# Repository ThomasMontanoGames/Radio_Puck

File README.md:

# Radio_Puck
Small STM32 based ethernet connected radio puck capable of full duplex transmit and receive as well as dual RX or dual TX. Capable of rates up to 1 Mbps and completely configurable for many kinds of different modes. This radio puck has been primarily designed to be your rubber duck that transmits a known signal while prototyping a receiver.

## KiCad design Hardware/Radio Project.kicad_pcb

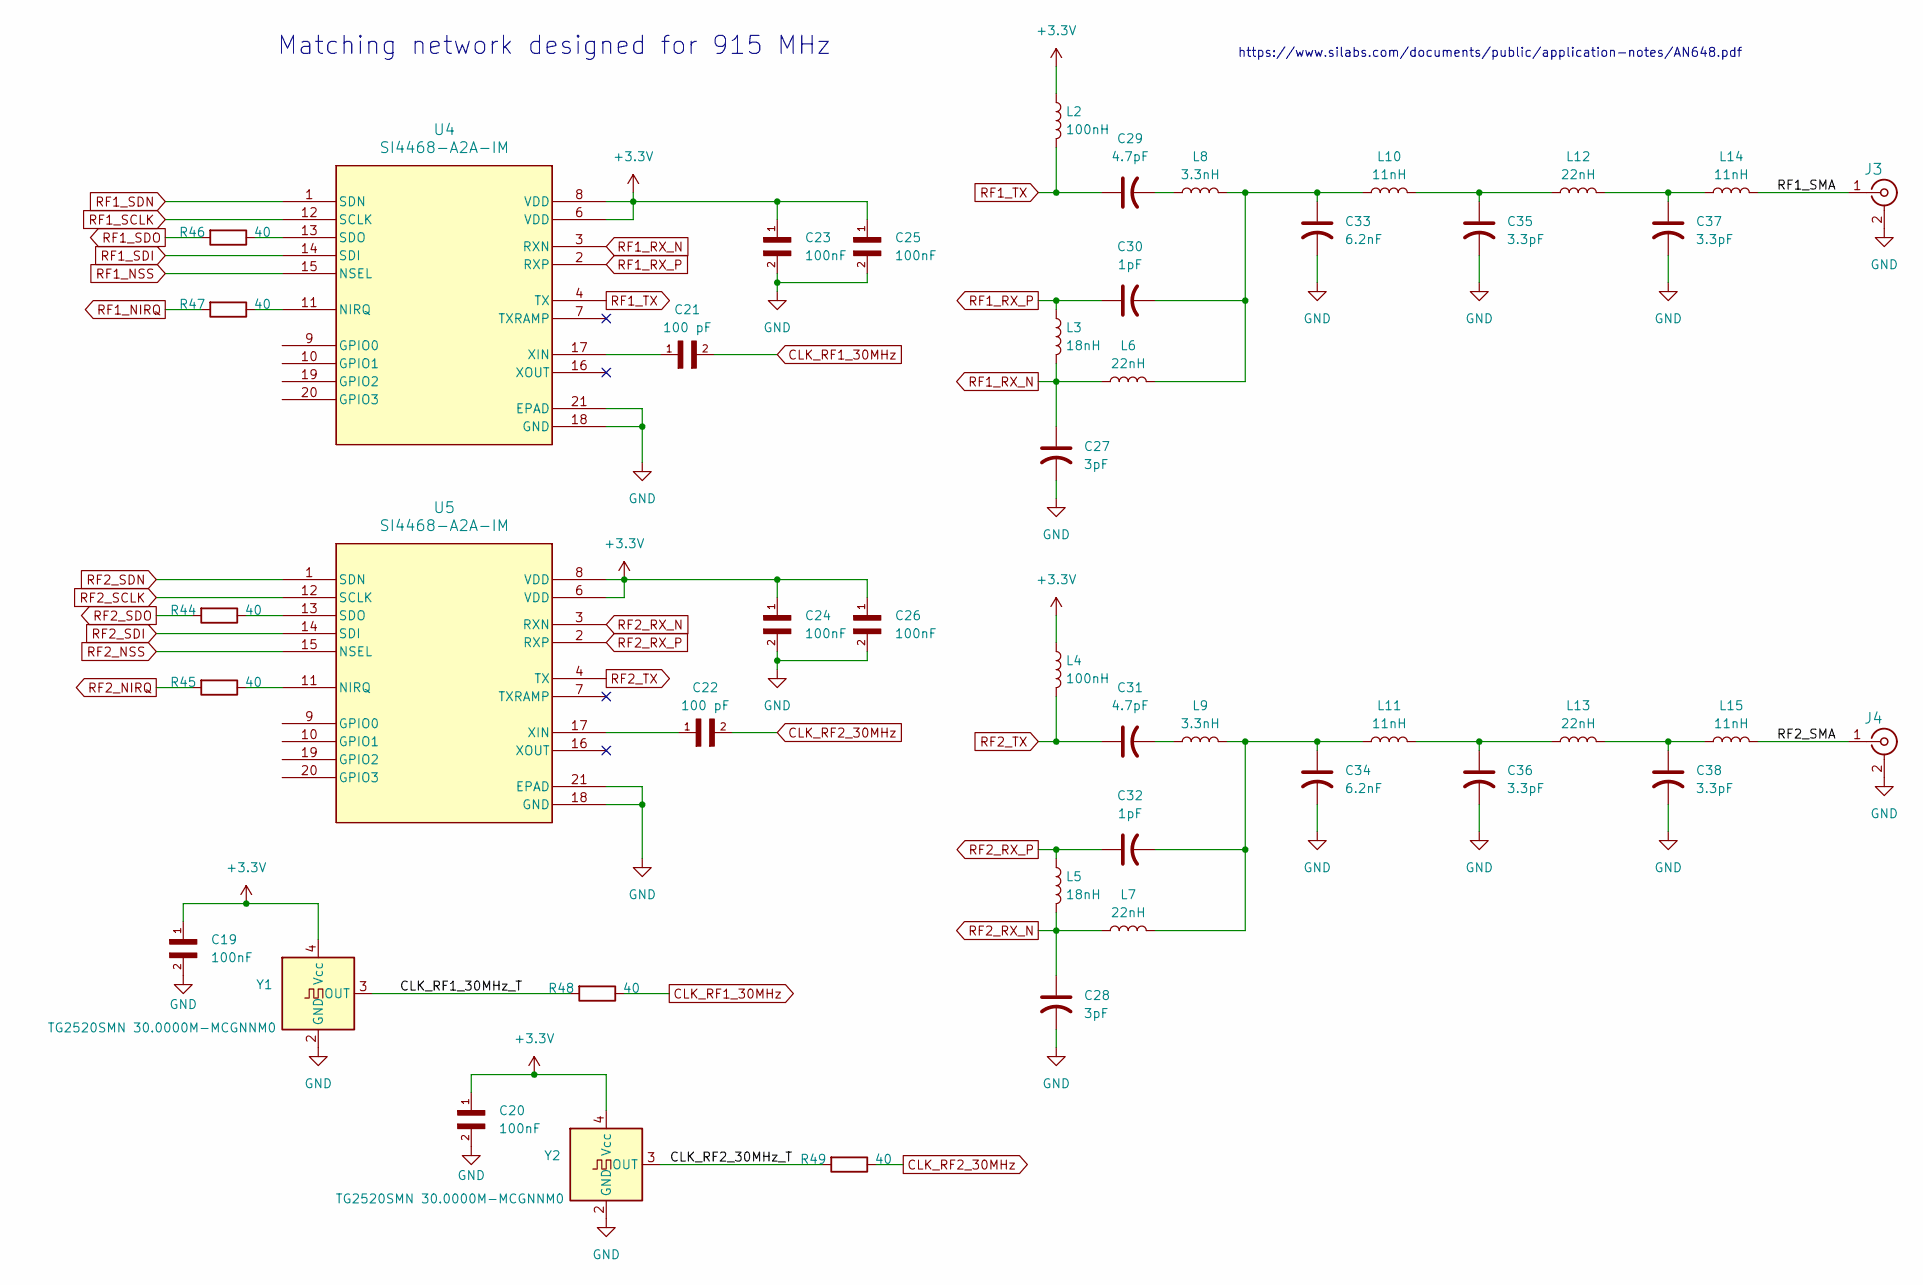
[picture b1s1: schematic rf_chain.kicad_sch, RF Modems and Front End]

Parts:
C19, C20, C23, C24, C25, C26: 100nF; CAPC10555_55N_KEM-L
C21, C22: 100 pF; CAPC1608X90N
C27, C28: 3pF; C_01005_0402Metric
C29, C31: 4.7pF; C_01005_0402Metric
C30, C32: 1pF; C_01005_0402Metric
C33, C34: 6.2nF; C_01005_0402Metric
C35, C36, C37, C38: 3.3pF; C_01005_0402Metric
J3, J4: 132225; CONN_132225_AMP
L2, L4: 100nH; L_0402_1005Metric
L3, L5: 18nH; L_0402_1005Metric
L6, L7, L12, L13: 22nH; L_0402_1005Metric
L8, L9: 3.3nH; L_0402_1005Metric
L10, L11, L14, L15: 11nH; L_0402_1005Metric
R44, R45, R46, R47, R48, R49: 40; R_0402_1005Metric
U4, U5: SI4468-A2A-IM; QFN50P400X400X90-21N
Y1, Y2: TG2520SMN 30.0000M-MCGNNM0; TG2520SMN

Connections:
+3.3V: C19.1, C20.1, C23.1, C24.1, C25.1, C26.1, L2.1, L4.1, U4.6 (VDD), U4.8 (VDD), U5.6 (VDD), U5.8 (VDD), Y1.4 (Vcc), Y2.4 (Vcc); also elsewhere on the board
/RF Chain/CLK_RF1_30MHz_T: R48.2, Y1.3 (OUT)
/RF Chain/CLK_RF2_30MHz_T: R49.2, Y2.3 (OUT)
/RF Chain/RF1_SMA: J3.1, L14.2
/RF Chain/RF2_SMA: J4.1, L15.2
CLK_RF1_30MHz: C21.2, R48.1
CLK_RF2_30MHz: C22.2, R49.1
GND: C19.2, C20.2, C23.2, C24.2, C25.2, C26.2, C27.2, C28.2, C33.2, C34.2, C35.2, C36.2, C37.2, C38.2, J3.2, J4.2, U4.18 (GND), U4.21 (EPAD), U5.18 (GND), U5.21 (EPAD), Y1.2 (GND), Y2.2 (GND); also elsewhere on the board
unnamed: C29.2, L8.1
unnamed: C30.2, C33.1, L6.2, L8.2, L10.1
unnamed: C31.2, L9.1
unnamed: C32.2, C34.1, L7.2, L9.2, L11.1
unnamed: C35.1, L10.2, L12.1
unnamed: C36.1, L11.2, L13.1
unnamed: C37.1, L12.2, L14.1
unnamed: C38.1, L13.2, L15.1
unnamed: R47.1, U4.11 (NIRQ)
unnamed: R46.1, U4.13 (SDO)
unnamed: C21.1, U4.17 (XIN)
unnamed: R45.1, U5.11 (NIRQ)
unnamed: R44.1, U5.13 (SDO)
unnamed: C22.1, U5.17 (XIN)
RF1_NIRQ: R47.2; also elsewhere on the board
RF1_NSS: U4.15 (NSEL); also elsewhere on the board
RF1_RX_N: C27.1, L3.2, L6.1, U4.3 (RXN)
RF1_RX_P: C30.1, L3.1, U4.2 (RXP)
RF1_SCLK: U4.12 (SCLK); also elsewhere on the board
RF1_SDI: U4.14 (SDI); also elsewhere on the board
RF1_SDN: U4.1 (SDN); also elsewhere on the board
RF1_SDO: R46.2; also elsewhere on the board
RF1_TX: C29.1, L2.2, U4.4 (TX)
RF2_NIRQ: R45.2; also elsewhere on the board
RF2_NSS: U5.15 (NSEL); also elsewhere on the board
RF2_RX_N: C28.1, L5.2, L7.1, U5.3 (RXN)
RF2_RX_P: C32.1, L5.1, U5.2 (RXP)
RF2_SCLK: U5.12 (SCLK); also elsewhere on the board
RF2_SDI: U5.14 (SDI); also elsewhere on the board
RF2_SDN: U5.1 (SDN); also elsewhere on the board
RF2_SDO: R44.2; also elsewhere on the board
RF2_TX: C31.1, L4.2, U5.4 (TX)

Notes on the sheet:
https://www.silabs.com/documents/public/application-notes/AN648.pdf
Matching network designed for 915 MHz

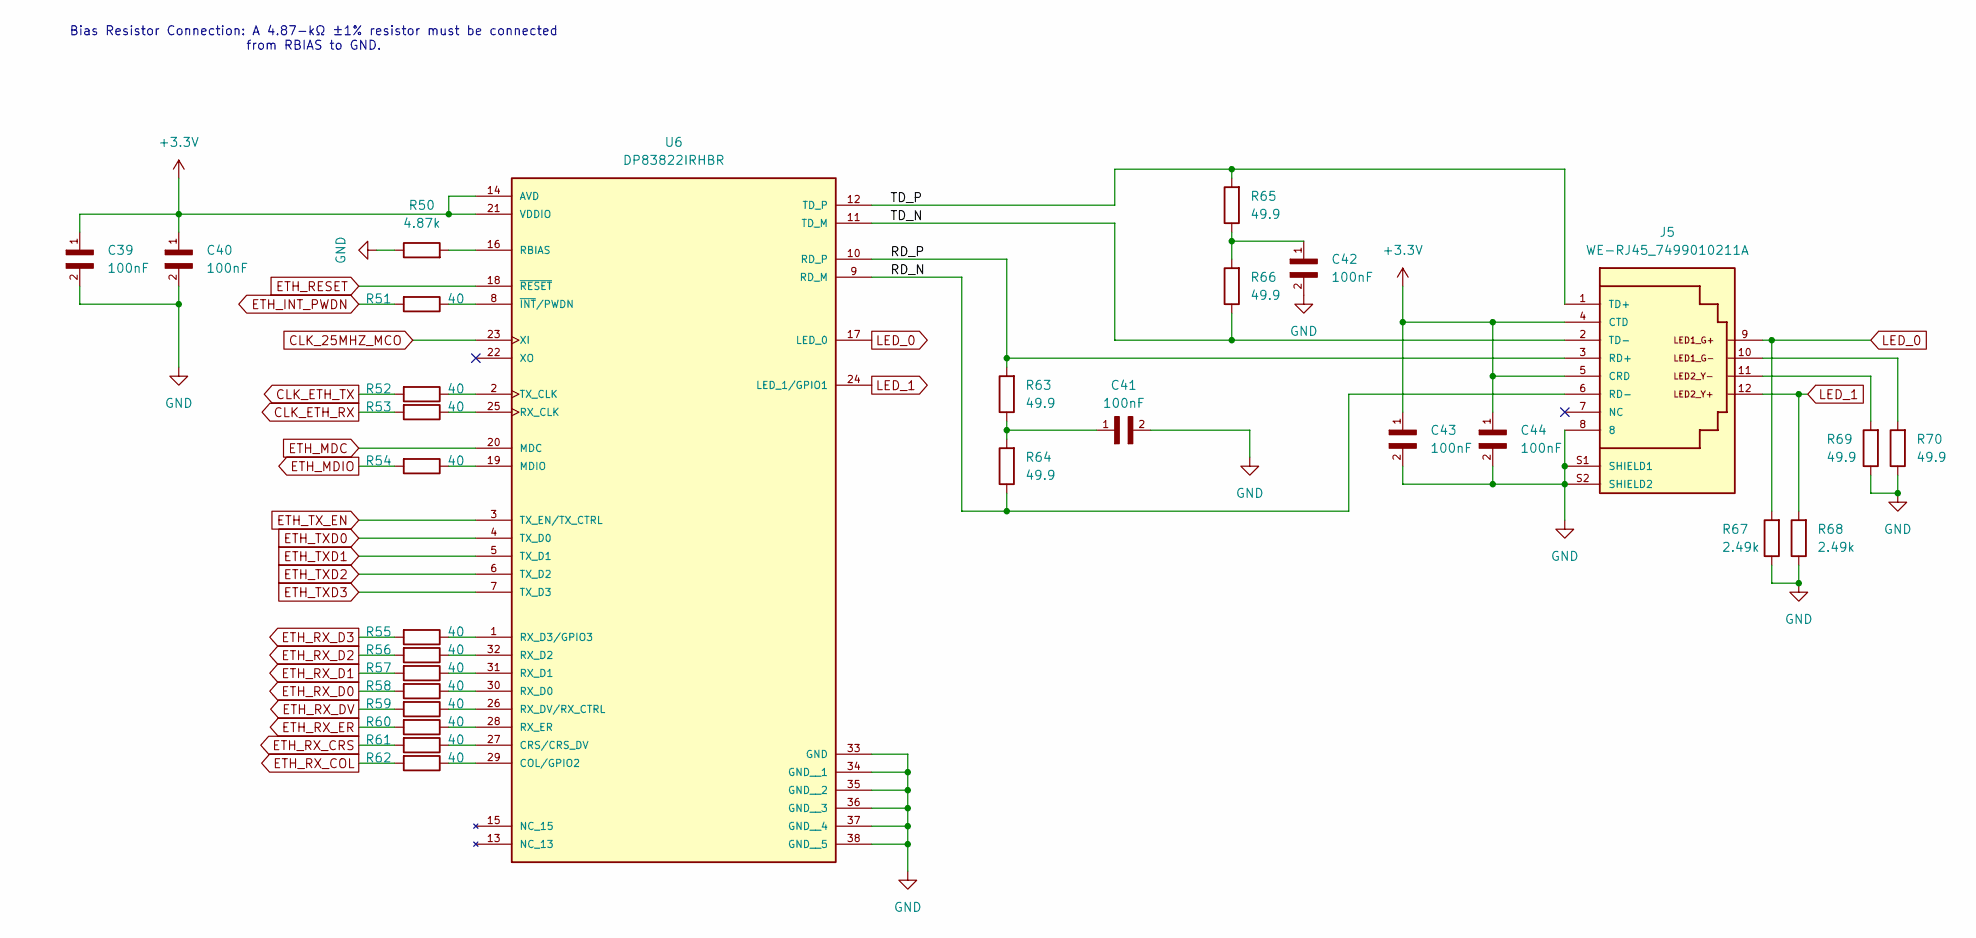
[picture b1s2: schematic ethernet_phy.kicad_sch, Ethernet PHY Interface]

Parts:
C39, C40, C41, C42, C43, C44: 100nF; CAPC10555_55N_KEM-L
J5: WE-RJ45_7499010211A; 7499010211A
R50: 4.87k; R_0402_1005Metric
R51, R52, R53, R54, R55, R56, R57, R58, R59, R60, R61, R62: 40; R_0402_1005Metric
R63, R64, R65, R66, R69, R70: 49.9; R_0402_1005Metric
R67, R68: 2.49k; R_0402_1005Metric
U6: DP83822IRHBR; IC_DP83822IRHBR; PARTREV 4223216/A 08/2016

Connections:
+3.3V: C39.1, C40.1, C43.1, C44.1, J5.4 (CTD), J5.5 (CRD), U6.14 (AVD), U6.21 (VDDIO); also elsewhere on the board
/Ethernet PHY/RD_N: J5.6 (RD-), R64.1, U6.9 (RD_M)
/Ethernet PHY/RD_P: J5.3 (RD+), R63.2, U6.10 (RD_P)
/Ethernet PHY/TD_N: J5.2 (TD-), R66.1, U6.11 (TD_M)
/Ethernet PHY/TD_P: J5.1 (TD+), R65.2, U6.12 (TD_P)
CLK_25MHZ_MCO: U6.23 (XI); also elsewhere on the board
CLK_ETH_RX: R53.2; also elsewhere on the board
CLK_ETH_TX: R52.2; also elsewhere on the board
ETH_INT_PWDN: R51.2; also elsewhere on the board
ETH_MDC: U6.20 (MDC); also elsewhere on the board
ETH_MDIO: R54.2; also elsewhere on the board
ETH_RESET: U6.18 (~RESET); also elsewhere on the board
ETH_RX_COL: R62.2; also elsewhere on the board
ETH_RX_CRS: R61.2; also elsewhere on the board
ETH_RX_D0: R58.2; also elsewhere on the board
ETH_RX_D1: R57.2; also elsewhere on the board
ETH_RX_D2: R56.2; also elsewhere on the board
ETH_RX_D3: R55.2; also elsewhere on the board
ETH_RX_DV: R59.2; also elsewhere on the board
ETH_RX_ER: R60.2; also elsewhere on the board
ETH_TXD0: U6.4 (TX_D0); also elsewhere on the board
ETH_TXD1: U6.5 (TX_D1); also elsewhere on the board
ETH_TXD2: U6.6 (TX_D2); also elsewhere on the board
ETH_TXD3: U6.7 (TX_D3); also elsewhere on the board
ETH_TX_EN: U6.3 (TX_EN/TX_CTRL); also elsewhere on the board
GND: C39.2, C40.2, C41.2, C42.2, C43.2, C44.2, J5.8, J5.S1 (SHIELD1), J5.S2 (SHIELD2), R50.1, R67.1, R68.1, R69.1, R70.1, U6.33 (GND), U6.34 (GND__1), U6.35 (GND__2), U6.36 (GND__3), U6.37 (GND__4), U6.38 (GND__5); also elsewhere on the board
LED_0: J5.9, R67.2, U6.17 (LED_0)
LED_1: J5.12, R68.2, U6.24 (LED_1/GPIO1)
unnamed: C41.1, R63.1, R64.2
unnamed: C42.1, R65.1, R66.2
unnamed: J5.10, R70.2
unnamed: J5.11, R69.2
unnamed: R62.1, U6.29 (COL/GPIO2)
unnamed: R61.1, U6.27 (CRS/CRS_DV)
unnamed: R54.1, U6.19 (MDIO)
unnamed: R50.2, U6.16 (RBIAS)
unnamed: R53.1, U6.25 (RX_CLK)
unnamed: R58.1, U6.30 (RX_D0)
unnamed: R57.1, U6.31 (RX_D1)
unnamed: R56.1, U6.32 (RX_D2)
unnamed: R55.1, U6.1 (RX_D3/GPIO3)
unnamed: R59.1, U6.26 (RX_DV/RX_CTRL)
unnamed: R60.1, U6.28 (RX_ER)
unnamed: R52.1, U6.2 (TX_CLK)
unnamed: R51.1, U6.8 (~INT/PWDN)

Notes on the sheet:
Bias Resistor Connection: A 4.87-kΩ ±1% resistor must be connected from RBIAS to GND.

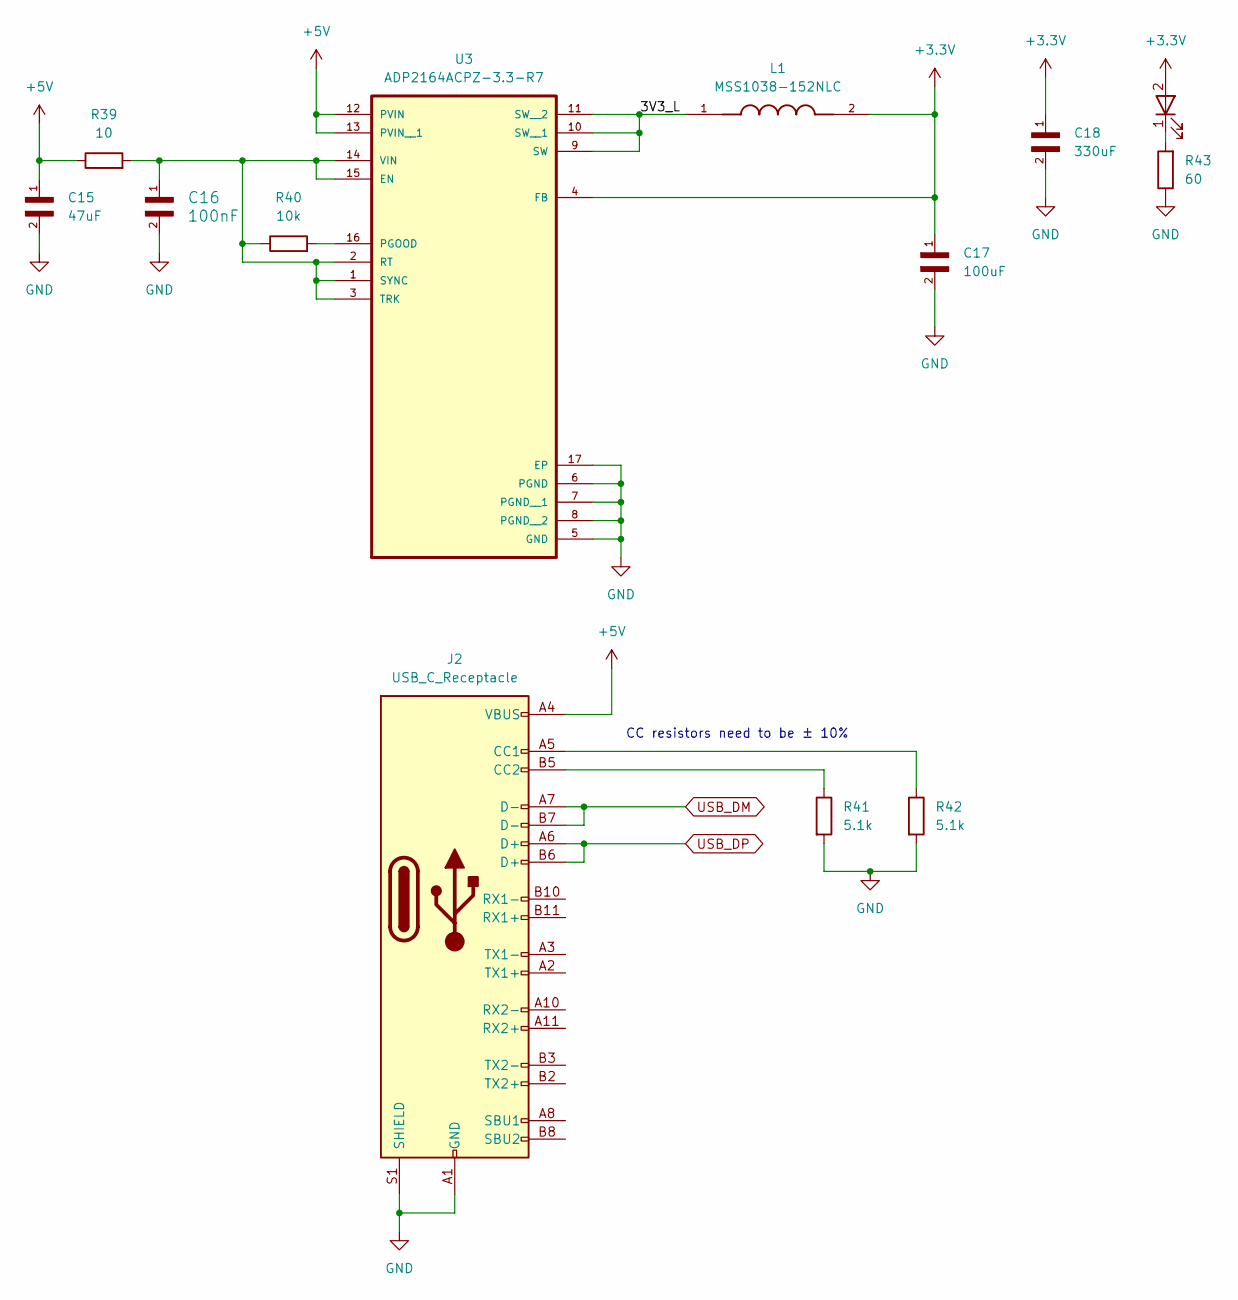
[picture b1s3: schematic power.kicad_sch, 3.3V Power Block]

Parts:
C15: 47uF; CAP_C3225X5R0J476M250AA; PARTREV 8/10/2022
C16: 100nF; CAPC10555_55N_KEM-L
C17: 100uF; CAP_C3225X5R0J107M250AB; PARTREV 8/10/2022
C18: 330uF; CAPPM7343X310N
J2: USB_C_Receptacle; USB_C_Receptacle_Amphenol_12401548E4-2A
L1: MSS1038-152NLC; L_Coilcraft_MSS1038-XXX; PARTREV 09/27/22
LED9: CMD17-21VGD/TR8; LED0805N_CML-M
R39: 10; R_0402_1005Metric
R40: 10k; R_0402_1005Metric
R41, R42: 5.1k; R_0402_1005Metric
R43: 60; R_0402_1005Metric
U3: ADP2164ACPZ-3.3-R7; QFN65P400X400X80-17N

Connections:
+3.3V: C17.1, C18.1, L1.2, LED9.2, U3.4 (FB); also elsewhere on the board
+5V: C15.1, J2.A4 (VBUS), J2.A9 (VBUS), J2.B4 (VBUS), J2.B9 (VBUS), R39.1, U3.12 (PVIN), U3.13 (PVIN__1)
/3V3 Power/3V3_L: L1.1, U3.9 (SW), U3.10 (SW__1), U3.11 (SW__2)
GND: C15.2, C16.2, C17.2, C18.2, J2.A1 (GND), J2.A12 (GND), J2.B1 (GND), J2.B12 (GND), J2.S1 (SHIELD), R41.2, R42.2, R43.1, U3.5 (GND), U3.6 (PGND), U3.7 (PGND__1), U3.8 (PGND__2), U3.17 (EP); also elsewhere on the board
unnamed: J2.A5 (CC1), R42.1
unnamed: J2.B5 (CC2), R41.1
unnamed: LED9.1, R43.2
unnamed: C16.1, R39.2, R40.1, U3.1 (SYNC), U3.2 (RT), U3.3 (TRK), U3.14 (VIN), U3.15 (EN)
unnamed: R40.2, U3.16 (PGOOD)
USB_DM: J2.A7 (D-), J2.B7 (D-); also elsewhere on the board
USB_DP: J2.A6 (D+), J2.B6 (D+); also elsewhere on the board

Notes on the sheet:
CC resistors need to be ± 10%

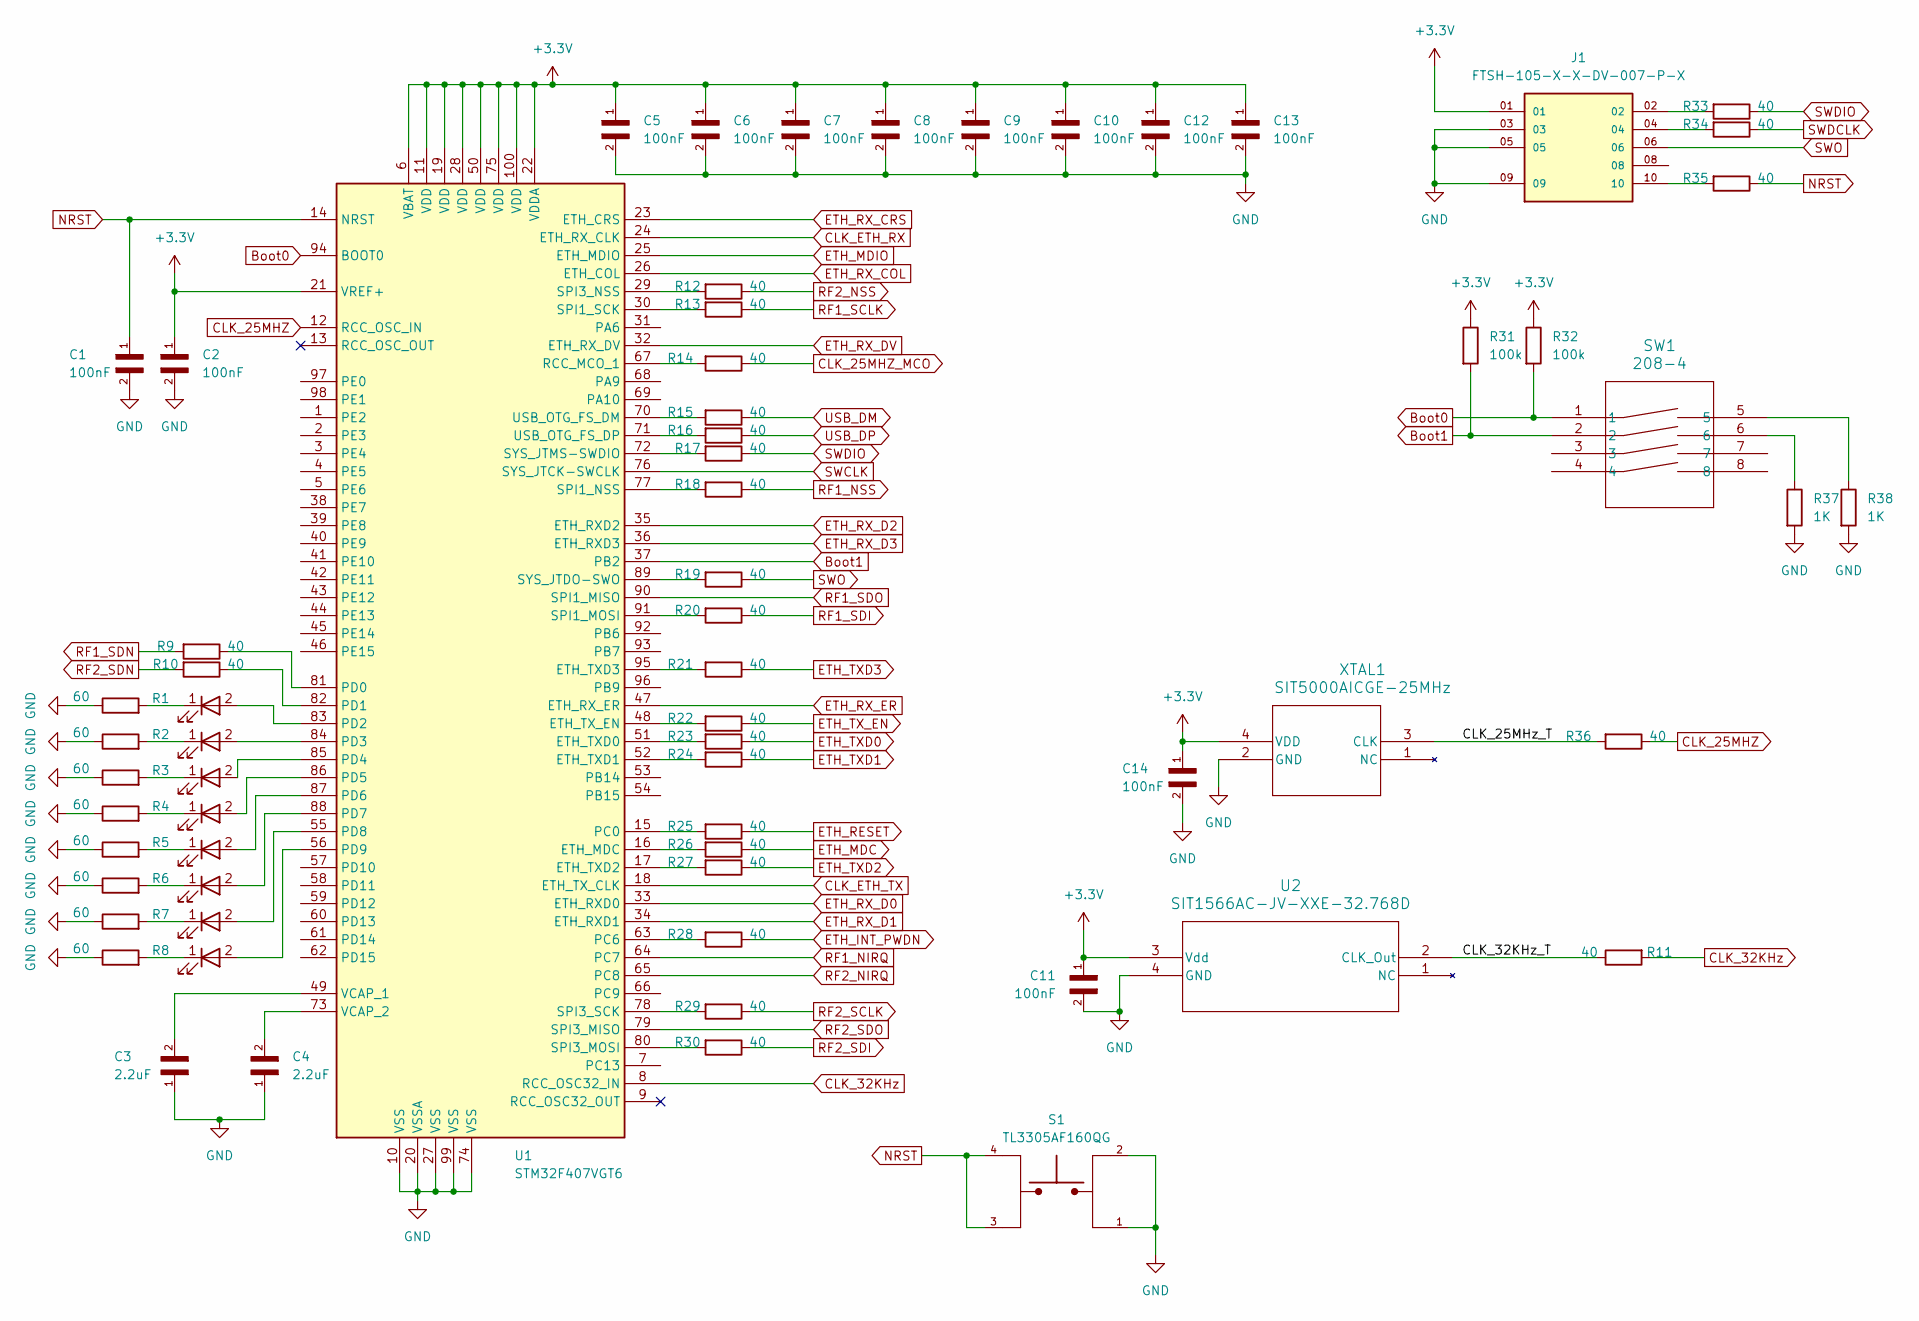
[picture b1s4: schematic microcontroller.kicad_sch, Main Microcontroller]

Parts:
C1, C2, C5, C6, C7, C8, C9, C10, C11, C12, C13, C14: 100nF; CAPC10555_55N_KEM-L
C3, C4: 2.2uF; CAPC2012X140N
J1: FTSH-105-X-X-DV-007-P-X; SAMTEC_FTSH-105-X-X-DV-007-P-X; PARTREV H
LED1, LED2, LED3, LED4, LED5, LED6, LED7, LED8: CMD17-21VGD/TR8; LED0805N_CML-M
R1, R2, R3, R4, R5, R6, R7, R8: 60; R_0402_1005Metric
R9, R10, R11, R12, R13, R14, R15, R16, R17, R18, R19, R20, R21, R22, R23, R24, R25, R26, R27, R28, R29, R30, R33, R34, R35, R36: 40; R_0402_1005Metric
R31, R32: 100k; R_0402_1005Metric
R37, R38: 1K; R_0402_1005Metric
S1: TL3305AF160QG; SW_TL3305AF160QG; PARTREV C
SW1: 208-4; DIP8_208-4_CTS
U1: STM32F407VGT6; LQFP-100_14x14mm_P0.5mm
U2: SIT1566AC-JV-XXE-32.768D; BGA_E-32.768D_SIT
XTAL1: SIT5000AICGE-25MHz; SIT5000_2.7x2.4_SIT-M

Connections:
+3.3V: C2.1, C5.1, C6.1, C7.1, C8.1, C9.1, C10.1, C11.1, C12.1, C13.1, C14.1, J1.01, R31.1, R32.1, U1.6 (VBAT), U1.11 (VDD), U1.19 (VDD), U1.21 (VREF+), U1.22 (VDDA), U1.28 (VDD), U1.50 (VDD), U1.75 (VDD), U1.100 (VDD), U2.3 (Vdd), XTAL1.4 (VDD); also elsewhere on the board
/Microcontroller/CLK_25MHz_T: R36.2, XTAL1.3 (CLK)
/Microcontroller/CLK_32KHz_T: R11.1, U2.2 (CLK_Out)
Boot0: R32.2, SW1.1, U1.94 (BOOT0)
Boot1: R31.2, SW1.2, U1.37 (PB2)
CLK_25MHZ: R36.1, U1.12 (RCC_OSC_IN)
CLK_25MHZ_MCO: R14.1; also elsewhere on the board
CLK_32KHz: R11.2, U1.8 (RCC_OSC32_IN)
CLK_ETH_RX: U1.24 (ETH_RX_CLK); also elsewhere on the board
CLK_ETH_TX: U1.18 (ETH_TX_CLK); also elsewhere on the board
ETH_INT_PWDN: R28.1; also elsewhere on the board
ETH_MDC: R26.1; also elsewhere on the board
ETH_MDIO: U1.25 (ETH_MDIO); also elsewhere on the board
ETH_RESET: R25.1; also elsewhere on the board
ETH_RX_COL: U1.26 (ETH_COL); also elsewhere on the board
ETH_RX_CRS: U1.23 (ETH_CRS); also elsewhere on the board
ETH_RX_D0: U1.33 (ETH_RXD0); also elsewhere on the board
ETH_RX_D1: U1.34 (ETH_RXD1); also elsewhere on the board
ETH_RX_D2: U1.35 (ETH_RXD2); also elsewhere on the board
ETH_RX_D3: U1.36 (ETH_RXD3); also elsewhere on the board
ETH_RX_DV: U1.32 (ETH_RX_DV); also elsewhere on the board
ETH_RX_ER: U1.47 (ETH_RX_ER); also elsewhere on the board
ETH_TXD0: R23.1; also elsewhere on the board
ETH_TXD1: R24.1; also elsewhere on the board
ETH_TXD2: R27.1; also elsewhere on the board
ETH_TXD3: R21.1; also elsewhere on the board
ETH_TX_EN: R22.1; also elsewhere on the board
GND: C1.2, C2.2, C3.1, C4.1, C5.2, C6.2, C7.2, C8.2, C9.2, C10.2, C11.2, C12.2, C13.2, C14.2, J1.03, J1.05, J1.09, R1.1, R2.1, R3.1, R4.1, R5.1, R6.1, R7.1, R8.1, R37.2, R38.2, S1.1, S1.2, U1.10 (VSS), U1.20 (VSSA), U1.27 (VSS), U1.74 (VSS), U1.99 (VSS), U2.4 (GND), XTAL1.2 (GND); also elsewhere on the board
NRST: C1.1, R35.1, S1.3, S1.4, U1.14 (NRST)
unnamed: J1.02, R33.2
unnamed: J1.04, R34.2
unnamed: J1.10, R35.2
unnamed: LED1.1, R1.2
unnamed: LED2.1, R2.2
unnamed: LED3.1, R3.2
unnamed: LED4.1, R4.2
unnamed: LED5.1, R5.2
unnamed: LED6.1, R6.2
unnamed: LED7.1, R7.2
unnamed: LED8.1, R8.2
unnamed: R37.1, SW1.6
unnamed: R38.1, SW1.5
unnamed: R12.2, U1.29 (SPI3_NSS)
unnamed: R13.2, U1.30 (SPI1_SCK)
unnamed: R14.2, U1.67 (RCC_MCO_1)
unnamed: R15.2, U1.70 (USB_OTG_FS_DM)
unnamed: R16.2, U1.71 (USB_OTG_FS_DP)
unnamed: R17.2, U1.72 (SYS_JTMS-SWDIO)
unnamed: R18.2, U1.77 (SPI1_NSS)
unnamed: R19.2, U1.89 (SYS_JTDO-SWO)
unnamed: R20.2, U1.91 (SPI1_MOSI)
unnamed: R21.2, U1.95 (ETH_TXD3)
unnamed: R22.2, U1.48 (ETH_TX_EN)
unnamed: R23.2, U1.51 (ETH_TXD0)
unnamed: R24.2, U1.52 (ETH_TXD1)
unnamed: R25.2, U1.15 (PC0)
unnamed: R26.2, U1.16 (ETH_MDC)
unnamed: R27.2, U1.17 (ETH_TXD2)
unnamed: R28.2, U1.63 (PC6)
unnamed: R29.2, U1.78 (SPI3_SCK)
unnamed: R30.2, U1.80 (SPI3_MOSI)
unnamed: R9.1, U1.81 (PD0)
unnamed: R10.1, U1.82 (PD1)
unnamed: LED1.2, U1.83 (PD2)
unnamed: LED2.2, U1.84 (PD3)
unnamed: LED3.2, U1.85 (PD4)
unnamed: LED4.2, U1.86 (PD5)
unnamed: LED5.2, U1.87 (PD6)
unnamed: LED6.2, U1.88 (PD7)
unnamed: LED7.2, U1.55 (PD8)
unnamed: LED8.2, U1.56 (PD9)
unnamed: C3.2, U1.49 (VCAP_1)
unnamed: C4.2, U1.73 (VCAP_2)
RF1_NIRQ: U1.64 (PC7); also elsewhere on the board
RF1_NSS: R18.1; also elsewhere on the board
RF1_SCLK: R13.1; also elsewhere on the board
RF1_SDI: R20.1; also elsewhere on the board
RF1_SDN: R9.2; also elsewhere on the board
RF1_SDO: U1.90 (SPI1_MISO); also elsewhere on the board
RF2_NIRQ: U1.65 (PC8); also elsewhere on the board
RF2_NSS: R12.1; also elsewhere on the board
RF2_SCLK: R29.1; also elsewhere on the board
RF2_SDI: R30.1; also elsewhere on the board
RF2_SDN: R10.2; also elsewhere on the board
RF2_SDO: U1.79 (SPI3_MISO); also elsewhere on the board
SWCLK: U1.76 (SYS_JTCK-SWCLK)
SWDCLK: R34.1
SWDIO: R17.1, R33.1
SWO: J1.06, R19.1
USB_DM: R15.1; also elsewhere on the board
USB_DP: R16.1; also elsewhere on the board

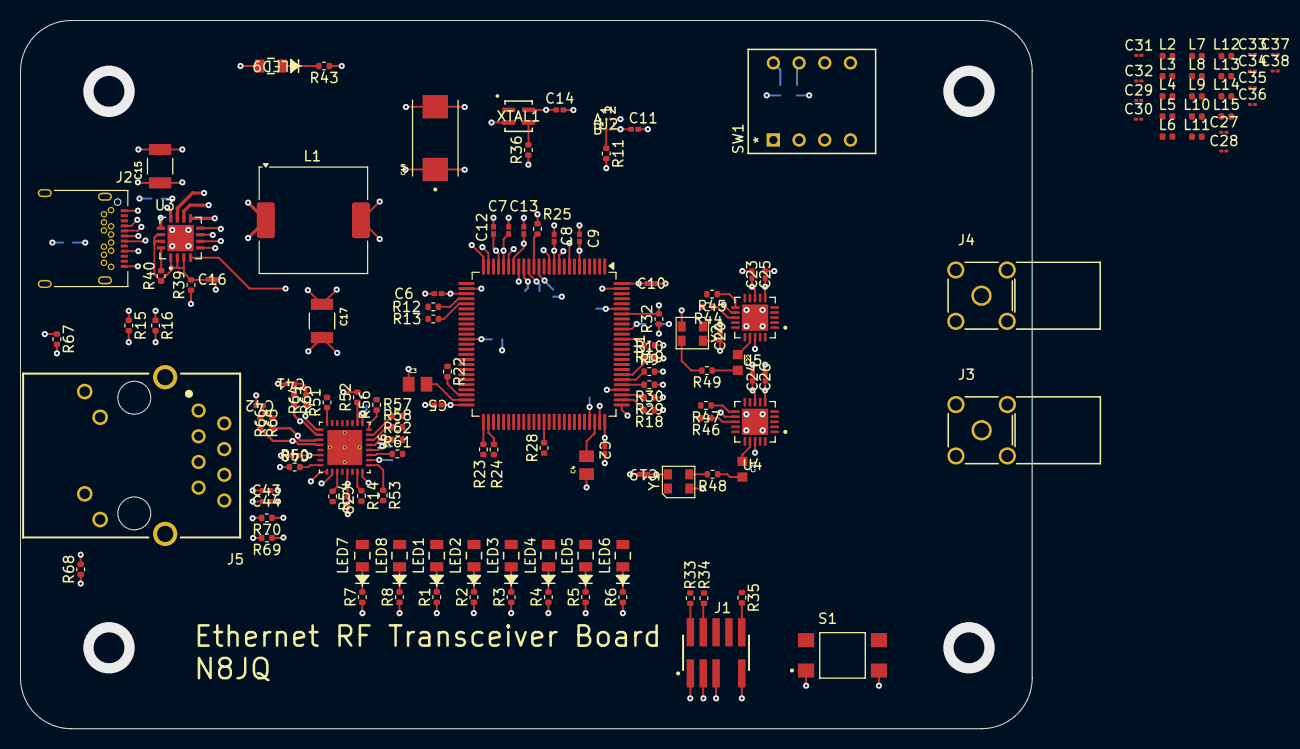
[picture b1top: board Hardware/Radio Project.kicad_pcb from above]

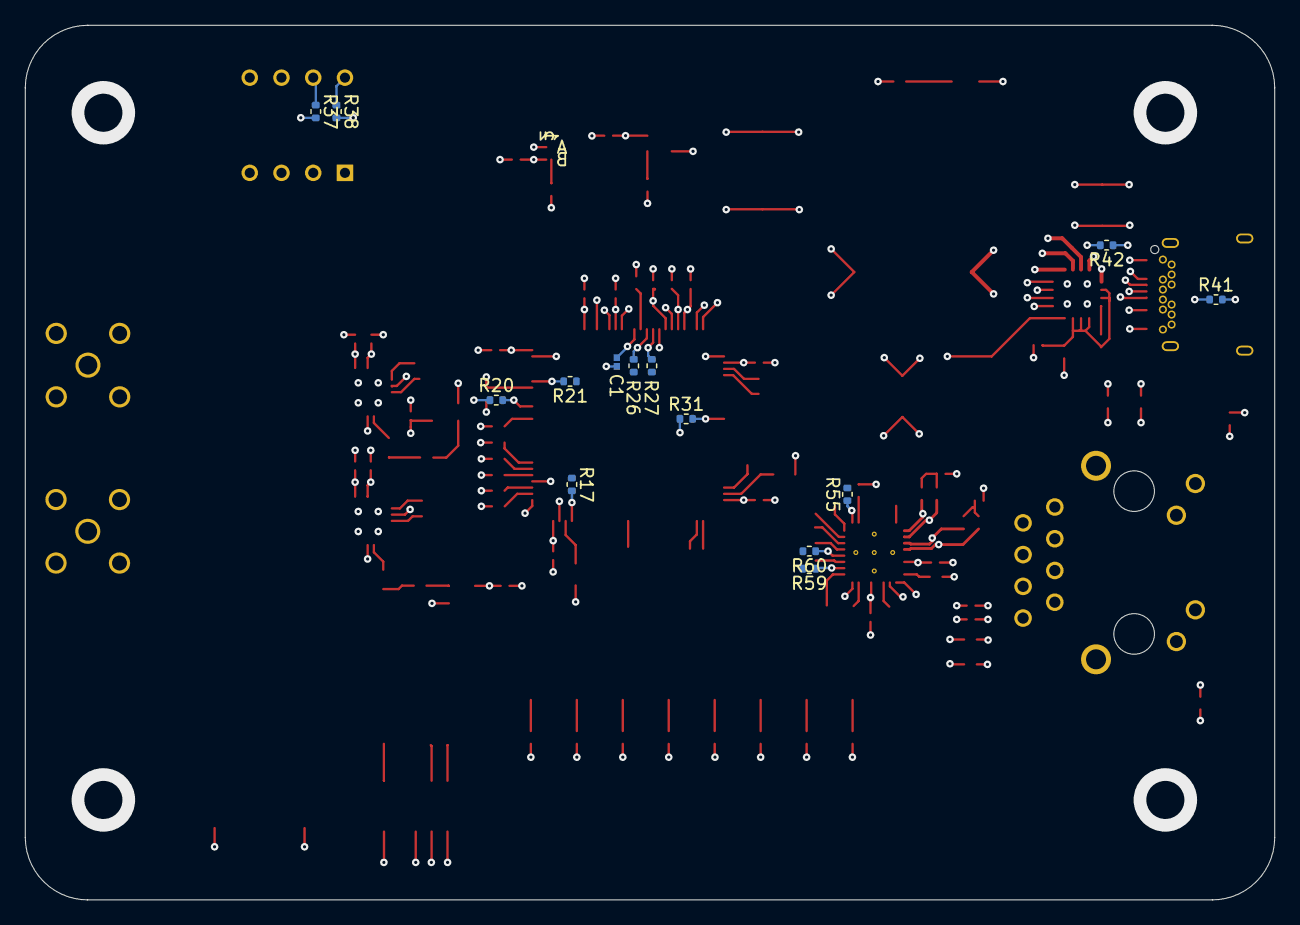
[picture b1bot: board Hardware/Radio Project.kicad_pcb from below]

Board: 8 copper layers, 100.0 x 70.0 mm, 154 parts (14 on the bottom side), 145 nets.

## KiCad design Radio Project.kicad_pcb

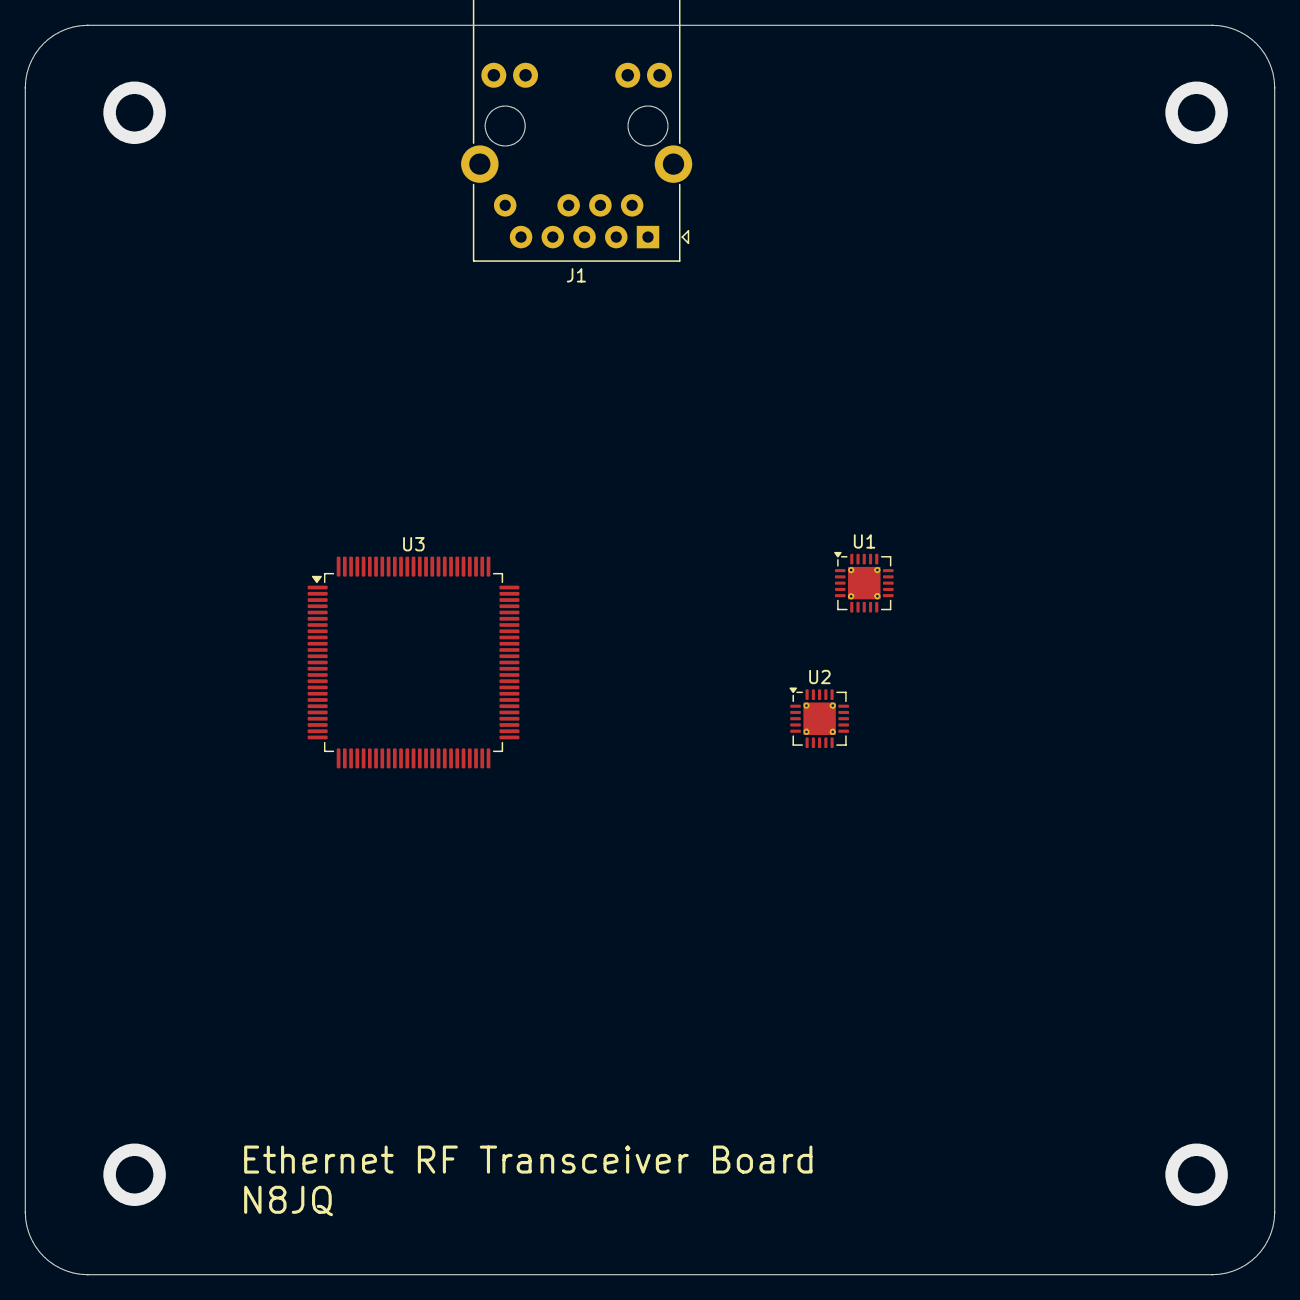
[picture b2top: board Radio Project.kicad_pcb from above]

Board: 2 copper layers, 100.0 x 100.0 mm, 4 parts (0 on the bottom side), 4 nets, no tracks yet.

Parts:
J1: RJ45_Abracon_ARJP11A-MASA-B-A-EMU2; RJ45_Abracon_ARJP11A-MA_Horizontal
U1, U2: Si4464; QFN-20-1EP_4x4mm_P0.5mm_EP2.6x2.6mm_ThermalVias
U3: STM32F407VGT6; LQFP-100_14x14mm_P0.5mm

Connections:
+3.3V: U1.6 (VDD), U1.8 (VDD), U2.6 (VDD), U2.8 (VDD), U3.6 (VBAT), U3.11 (VDD), U3.19 (VDD), U3.22 (VDDA), U3.28 (VDD), U3.50 (VDD), U3.75 (VDD), U3.100 (VDD)
GND: U3.10 (VSS), U3.20 (VSSA), U3.27 (VSS), U3.74 (VSS), U3.99 (VSS)
unnamed: U1.18 (GND), U1.21 (GND)
unnamed: U2.18 (GND), U2.21 (GND)

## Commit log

2025-06-22 Initial repo setup including firmware initialization and vscode config
2025-06-22 added SWD header and dip switches for boot modes
2025-06-22 Added 3.3V power connections and a USB-C connector for +5V
2025-06-23 added filtering caps, bulk decoupling caps, and power LED
2025-06-23 added SMA connectors and external connections sheet
2025-06-23 shutdown pin connection to RF chain
2025-06-24 .gitignore update
2025-06-24 Ethernet PHY and RJ45 connector
2025-06-24 Finished Ethernet connection between MAC and PHY
2025-06-24 Added high power USB-C Connection (5V @ 3A)
2025-06-25 git ignore update
2025-06-25 Added oscillators, reset button, and finalized ETH connection
2025-06-25 changed to SI4468, added 30 MHz oscillators, and connected it to MCU
2025-06-25 fixed incorrect naming on RF clk and connected RF NIRQ lines
2025-06-26 gitignore update
2025-06-26 added item numbers to BOM settings
2025-06-26 added RF matching network and added all 16 layers to stackup
2025-06-26 connected USB 2.0 data pins
2025-06-26 Added 5V plane
2025-06-27 updated USB pin labels
2025-06-30 added stackup doc and reduced board to 10 layers
2025-06-30 initial 8 layer layout with power decoupling connections
2025-06-30 Placed termination resistors
2025-06-30 ray tracing render of board
2025-07-07 fixed USB data lines and directory hierarchy
2025-07-08 diff pair routing for ethernet
